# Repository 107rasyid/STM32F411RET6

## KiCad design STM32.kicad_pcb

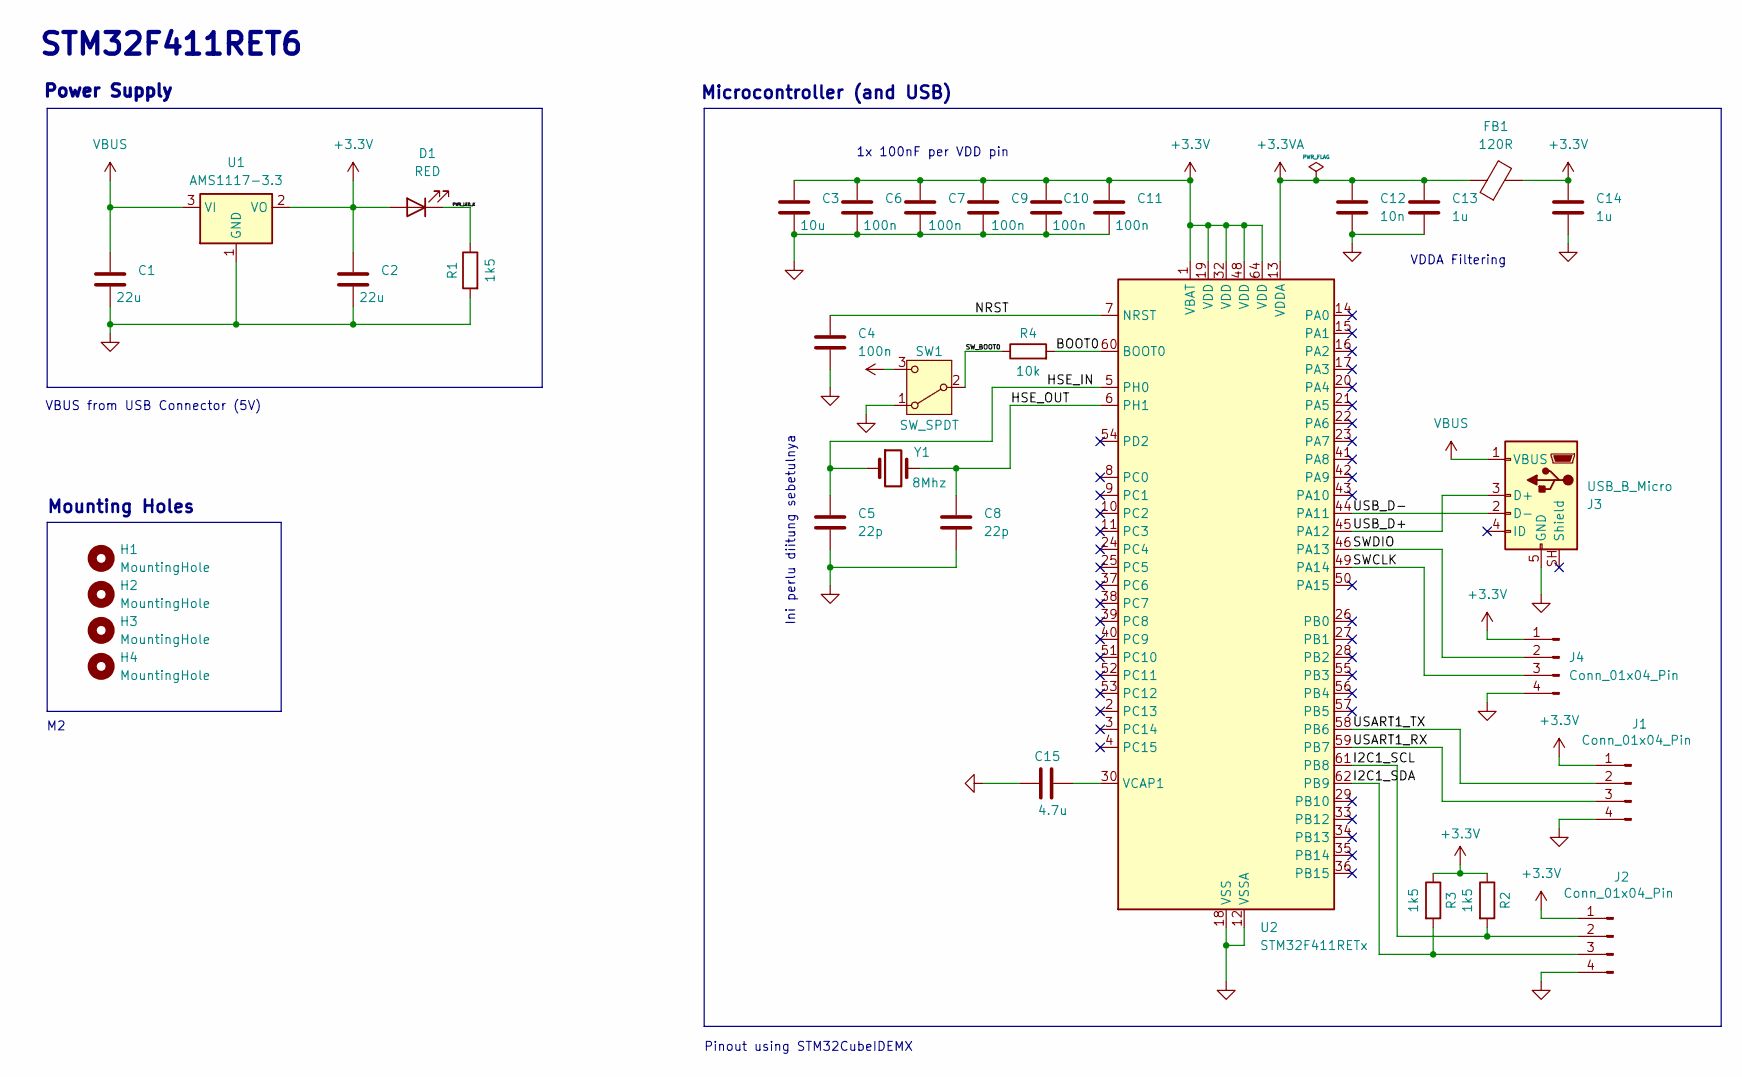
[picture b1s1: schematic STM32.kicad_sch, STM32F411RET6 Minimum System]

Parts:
C1, C2: 22u; C_0805_2012Metric
C3: 10u; C_0603_1608Metric
C4, C6, C7, C9, C10, C11: 100n; C_0402_1005Metric
C5, C8: 22p; C_0402_1005Metric
C12: 10n; C_0402_1005Metric
C13, C14: 1u; C_0402_1005Metric
C15: 4.7u; C_0402_1005Metric
D1: RED; LED_0603_1608Metric
FB1: 120R; L_0603_1608Metric
H1, H2, H3, H4: MountingHole; MountingHole_2.2mm_M2
J1, J2, J4: Conn_01x04_Pin; PinHeader_1x04_P2.54mm_Vertical
J3: USB_B_Micro; USB_Micro-B_Wuerth_629105150521
R1, R2, R3: 1k5; R_0402_1005Metric
R4: 10k; R_0402_1005Metric
SW1: SW_SPDT; SW_SPDT_PCM12
U1: AMS1117-3.3; SOT-223-3_TabPin2
U2: STM32F411RETx; LQFP-64_10x10mm_P0.5mm
Y1: 8Mhz; Crystal_HC49-4H_Vertical

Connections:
+3.3V: C2.1, C3.1, C6.1, C7.1, C9.1, C10.1, C11.1, C14.1, D1.2 (A), FB1.2, J1.1, J2.1, J4.1, R2.1, R3.1, SW1.3 (C), U1.2 (VO), U2.1 (VBAT), U2.19 (VDD), U2.32 (VDD), U2.48 (VDD), U2.64 (VDD)
+3.3VA: C12.1, C13.1, FB1.1, U2.13 (VDDA)
/BOOT0: R4.2, U2.60 (BOOT0)
/HSE_IN: C5.1, U2.5 (PH0), Y1.1
/HSE_OUT: C8.1, U2.6 (PH1), Y1.2
/I2C1_SCL: J2.2, R2.2, U2.61 (PB8)
/I2C1_SDA: J2.3, R3.2, U2.62 (PB9)
/NRST: C4.1, U2.7 (NRST)
/PWR_LED_K: D1.1 (K), R1.1
/SWCLK: J4.3, U2.49 (PA14)
/SWDIO: J4.2, U2.46 (PA13)
/SW_BOOT0: R4.1, SW1.2 (B)
/USART1_RX: J1.3, U2.59 (PB7)
/USART1_TX: J1.2, U2.58 (PB6)
/USB_D+: J3.3 (D+), U2.45 (PA12)
/USB_D-: J3.2 (D-), U2.44 (PA11)
GND: C1.2, C2.2, C3.2, C4.2, C5.2, C6.2, C7.2, C8.2, C9.2, C10.2, C11.2, C12.2, C13.2, C14.2, C15.2, J1.4, J2.4, J3.5 (GND), J4.4, R1.2, SW1.1 (A), U1.1 (GND), U2.12 (VSSA), U2.18 (VSS), U2.31 (VSS), U2.47 (VSS), U2.63 (VSS)
unnamed: C15.1, U2.30 (VCAP1)
VBUS: C1.1, J3.1 (VBUS), U1.3 (VI)

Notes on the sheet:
STM32F411RET6
Ini perlu diitung sebetulnya
Microcontroller (and USB)
Pinout using STM32CubeIDEMX
VDDA Filtering
Mounting Holes
VBUS from USB Connector (5V)
1x 100nF per VDD pin
Power Supply

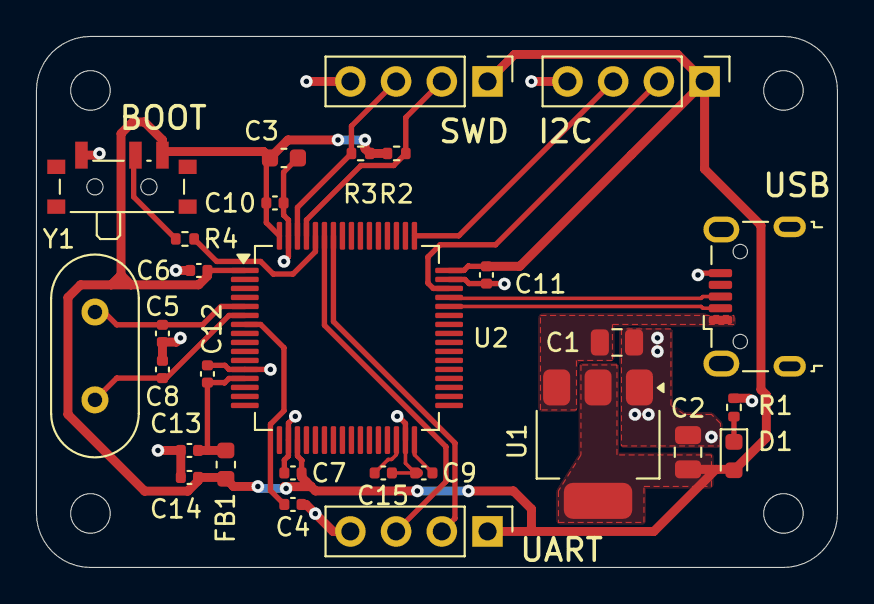
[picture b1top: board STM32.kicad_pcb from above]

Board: 2 copper layers, 44.5 x 29.5 mm, 33 parts (0 on the bottom side), 19 nets.
